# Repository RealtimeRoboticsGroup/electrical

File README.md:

# Realtime Robotic Group Electrical Repo

## License

This project is open-source hardware and is licensed under the **Solderpad Hardware License v2.1** (the "License"), which is a permissive license based on the **Apache License, Version 2.0**.

You may use this work under the terms of the Solderpad Hardware License v2.1, or, at your option, under the terms of the Apache License, Version 2.0.

- **Solderpad v2.1:** [Solderpad Hardware License v2.1 - Solderpad Hardware License](https://solderpad.org/licenses/SHL-2.1/)

- **Apache 2.0:** https://www.apache.org/licenses/LICENSE-2.0

**SPDX-License-Identifier:** `Apache-2.0 WITH SHL-2.1`

## License notes for included projects

### 1. For Schematics (Text Block)

Place this near your **Title Block** or in the **Notes** section of your first sheet.

> **LEGAL NOTICE** Copyright © 2026 [Your Name/Organization].
> Licensed under the Solderpad Hardware License v2.1 (the "License");
> you may not use this work except in compliance with the License.
> You may obtain a copy of the License at: [Solderpad Hardware License v2.1 - Solderpad Hardware License](https://solderpad.org/licenses/SHL-2.1/) SPDX-License-Identifier: Apache-2.0 WITH SHL-2.1

### 2. For PCB Silkscreen (Copper/Ink)

Space on a PCB is usually at a premium. You can use this condensed version on the back of the board (Bottom Silkscreen):

> **© 2026 [Your Name]** **Licensed under Solderpad v2.1** **[https://solderpad.org/SHL-2.1/](https://www.google.com/search?q=https://solderpad.org/SHL-2.1/)**

### 3. The OSHWA Logo (The "Gear")

If you want to signal that this is open-source hardware visually, it is common practice to add the **Open Source Hardware Logo** (a gear with a missing tooth) next to the license text. Most CAD libraries (like the SparkFun or Adafruit libraries) already have this logo as a "footprint" you can simply drop onto your board.

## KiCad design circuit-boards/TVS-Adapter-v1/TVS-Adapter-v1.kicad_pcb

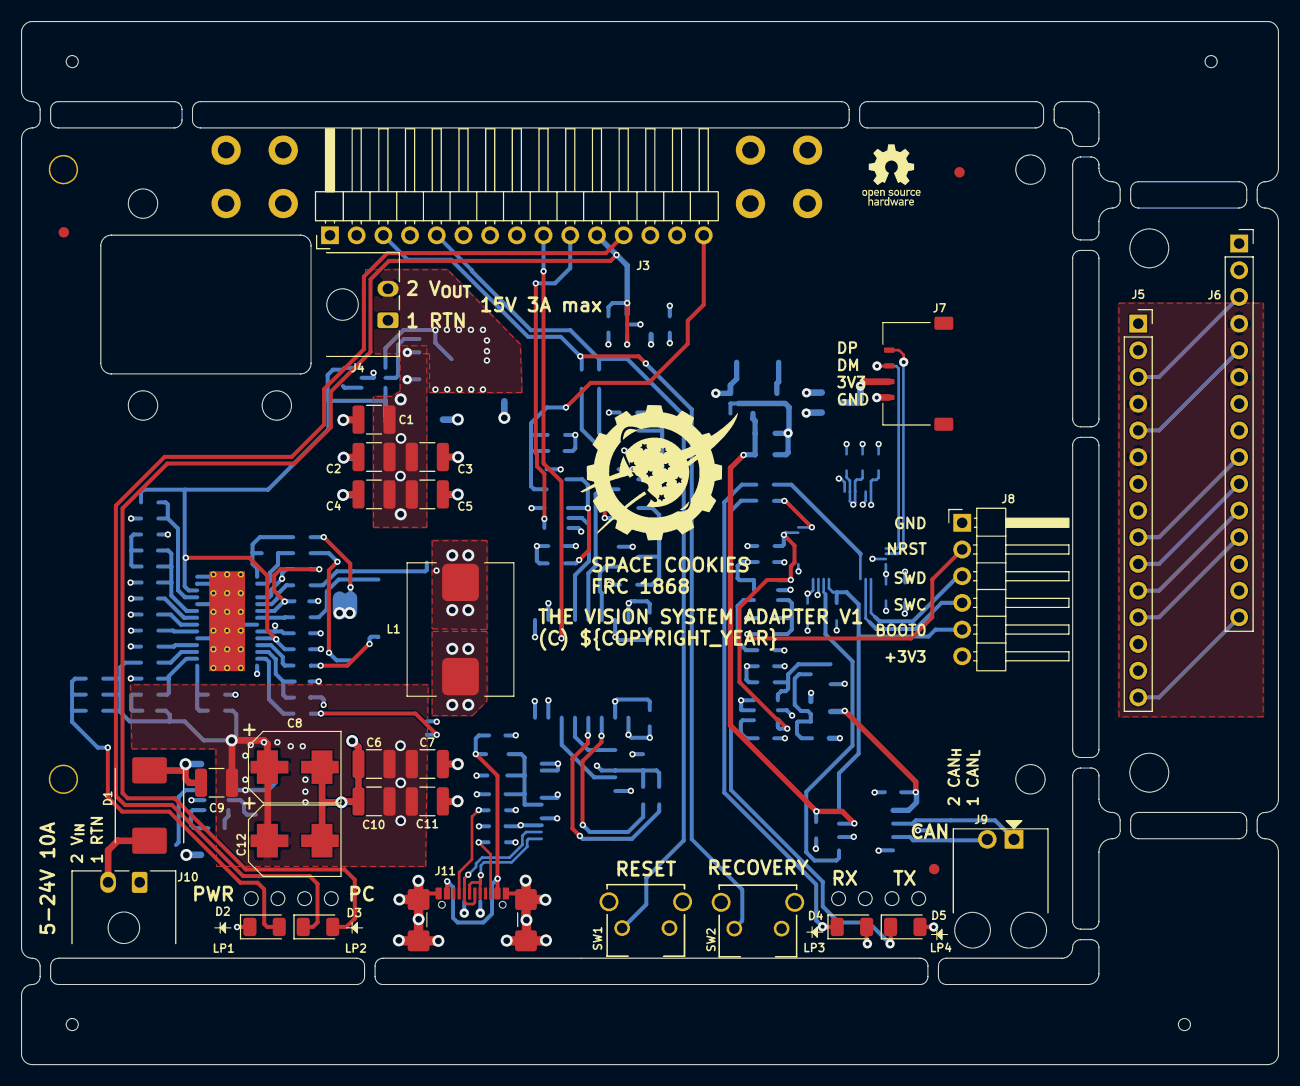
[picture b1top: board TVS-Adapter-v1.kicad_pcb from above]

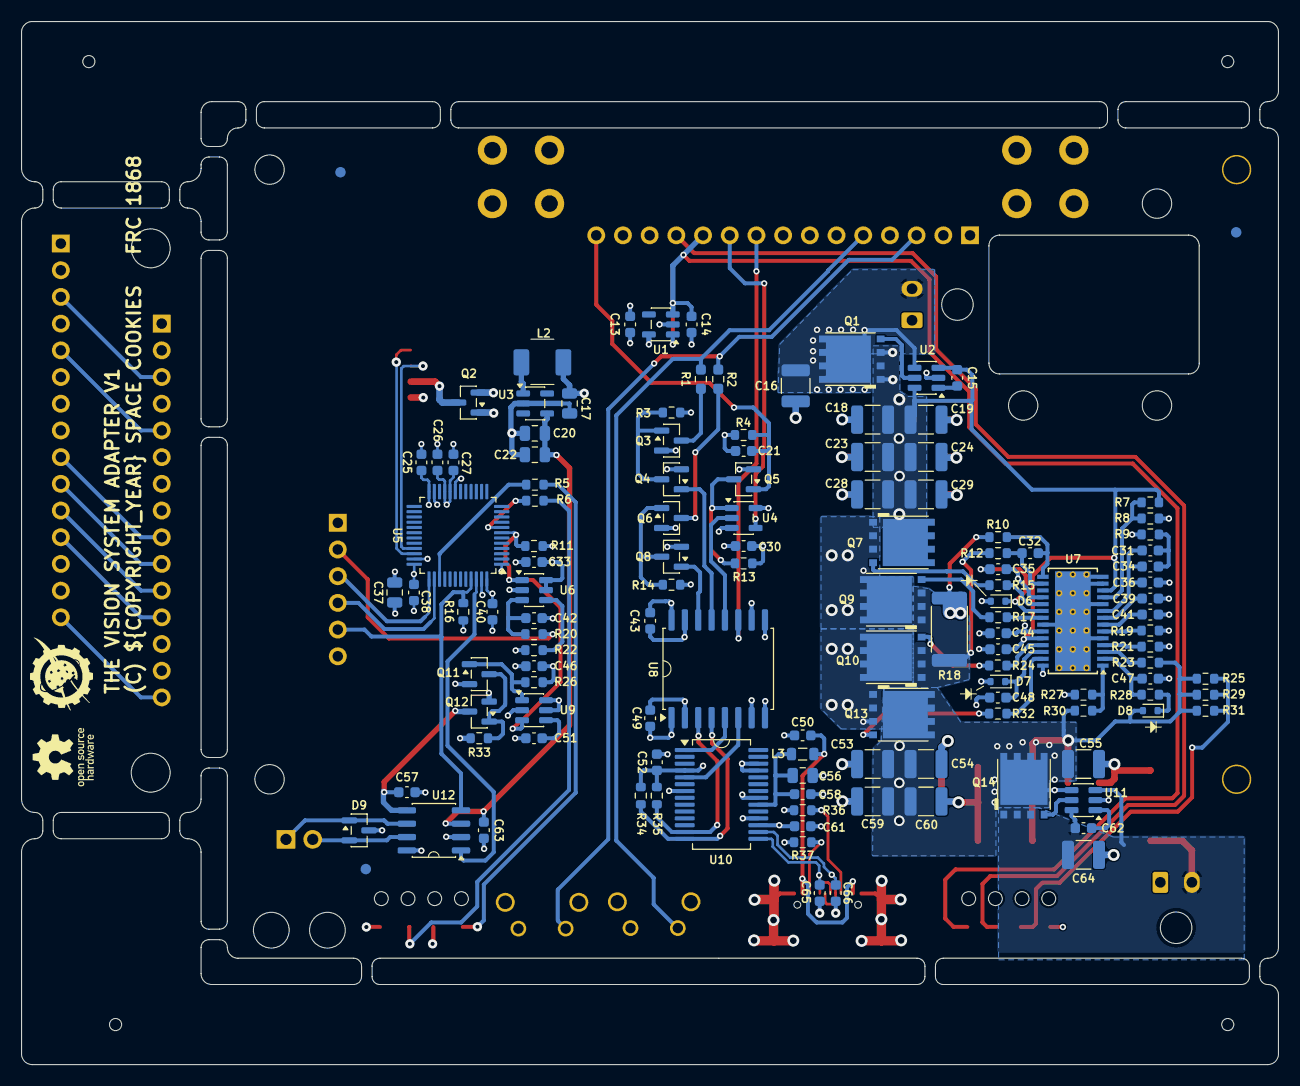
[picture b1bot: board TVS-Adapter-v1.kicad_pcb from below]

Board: 4 copper layers, 119.6 x 99.2 mm, 179 parts (127 on the bottom side), 99 nets.

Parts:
C1, C2, C3, C4, C5, C6, C7, C9, C10, C11, C16, C18, C19, C23, C24, C28, C29, C53, C54, C55, C59, C60, C64: 10uF-50V-10%-X7R-1210; C_1210_3225Metric
C8, C12: 47uF 50V; Panasonic-EEE-FT1H470AV
C13, C14, C44: 1uF-50V-10%-0603; C_0603_1608Metric
C15, C21, C25, C26, C27, C30, C33, C35, C38, C40, C43, C45, C46, C47, C48, C49, C51, C52, C57, C58, C61, C62, C63: 0.1uF-50V-10%-0603; C_0603_1608Metric
C17, C20, C22, C37, C56: 22uF-10%-16V-0805; C_0805_2012Metric
C31, C34: 5.6nF-10%-50V-0603; C_0603_1608Metric
C32, C65, C66: 47pF-50V-10%-0603; C_0603_1608Metric
C36: 270pF-10%-50V-0603; C_0603_1608Metric
C39, C42, C50: 15nF-10%-50V-0603; C_0603_1608Metric
C41: 150pF-50V-10%-0603; C_0603_1608Metric
D1: 24V; D_SMC_Littelfuse_DO-214AB
D2: PWR; LED_1206_3216Metric
D3: PC; LED_1206_3216Metric
D4: RX; LED_1206_3216Metric
D5: TX; LED_1206_3216Metric
D6, D7, D8: BAT54KFILM; D_SOD-523
D9: PESD1CAN; SOT-23
FID1, FID2, FID3, FID4, FID5, FID6: Fiducial; Fiducial_1mm_Mask3mm
H1, H2, H12, H13: 1.152mm ToolingHole; ToolingHole_1.152mm
H3, H4, H5, H7, H8, H10, H11: MountingHole; MountingHole_2.5mm
H6, H9: M3.7 MountingHole; MountingHole_3.7mm
J1, J2: Terminal; Keystone-7774
J3: NX CONTROL & UART; PinHeader_1x15_P2.54mm_Horizontal
J4: 15V; Molex_Micro-Fit_3.0_43650-0200_1x02_P3.00mm_Horizontal
J5, J6: NX CONTROL & UART; PinSocket_1x15_P2.54mm_Vertical
J7: USB1; Molex-PicoLatch-5040500491
J8: SWD; PinHeader_1x06_P2.54mm_Horizontal
J9: CAN1; Molex-70555-0001
J10: POWER; Molex_Micro-Fit_3.0_43650-0200_1x02_P3.00mm_Horizontal
J11: USB_C_Receptacle_USB2.0_14P; GCT-USB-C-USB4110-GF-A
L1: 2.2uH-19A-5.1mohm-20%; Koher-MDA1050
L2: 2.2uH-41mOhm-20%; KOHER-MDA4020-2R2M
L3: HZ0805E601R-10; L_0805_2012Metric
LOGO1: SPACE COOKIES LOGO; SPACE_COOKIES_LOGO_15mm
LOGO2: SPACE COOKIES LOGO; SPACE_COOKIES_LOGO_7mm
LP1, LP2, LP3, LP4: Light Pipe; Bivar-SLP3-150-100-F
Q1, Q10, Q13, Q14: CSD19534Q5A; TI-SON5x6
Q2, Q12: SI2301CDS-T1-GE3; SOT-23
Q3, Q4, Q5, Q6, Q8, Q11: BSS138; SOT-23
Q7, Q9: CSD17578Q5A; TI-SON5x6
R1, R2: 0R-1%-0603; R_0603_1608Metric_Pad0.98x0.95mm_HandSolder
R3, R4, R13, R14, R25, R29, R31, R34, R35, R36, R37: 5.1k-1%-0603; R_0603_1608Metric
R5, R6, R20: 1K-1%-0603; R_0603_1608Metric
R7: 357K-1%-0603; R_0603_1608Metric
R8: 20K-1%-0603; R_0603_1608Metric
R9: 5.9k-1%-0603; R_0603_1608Metric
R10, R12: 100R-1%-0603; R_0603_1608Metric
R11, R16, R19, R26: 13K-1%-0603; R_0603_1608Metric
R15, R17, R24, R32: 0R-1%-0603; R_0603_1608Metric
R18: 10mOhm-3W-1%-2512; R_2512_6332Metric
R21, R22, R27, R33: 93.1k-1%-0603; R_0603_1608Metric
R23: 2K-1%-0603; R_0603_1608Metric
R28: 10R0-1%-0603; R_0603_1608Metric
R30: 249K-1%-0603; R_0603_1608Metric
SW1: RESET; SW_TL1105VF100Q_EWI
SW2: RECOVERY; SW_TL1105VF100Q_EWI
U1: TLV70233DBVR; SOT-23-5
U2, U11: LM74700QDBVRQ1; SOT-23-6
U3: TPS613222ADBV; SOT-23-5
U4: SN74LVC1G125DBVR; SOT-23-5
U5: STM32G431CBTx; LQFP-48_7x7mm_P0.5mm
U6, U9: TPS3808G30DBVR; SOT-23-6
U7: LM5176PWPR; HTSSOP-28-1EP_4.4x9.7mm_P0.65mm_EP3.4x9.5mm_ThermalVias
U8: ISO6741DWR; SOIC-16W_7.5x10.3mm_P1.27mm
U10: FT232RNL; SSOP-28_5.3x10.2mm_P0.65mm
U12: TJA1051T/3/1J; SO-8_3.9x4.9mm_P1.27mm

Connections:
3V3_USB: C49.1, C52.1, C61.1, R34.2, R35.2, U8.1 (V_{CC1}), U8.7 (EN1), U10.4 (VCCIO), U10.17 (3V3OUT)
/3V3_BTN: C21.1, J3.15, Q5.1 (G), R4.2
/15V 3A Buck-Boost Power Supply/+V_OUT: C1.1, C2.1, C3.1, C4.1, C5.1, C15.1, C18.1, C19.1, C23.1, C24.1, C28.1, C29.1, C45.1, Q1.1 (S), Q1.2 (S), Q1.3 (S), Q7.5 (D), R7.1, U2.3 (EN), U2.6 (A), U7.12 (VOSNS), U7.24 (BIAS)
/15V 3A Buck-Boost Power Supply/HDRV1: Q13.4 (G), R32.2
/15V 3A Buck-Boost Power Supply/HDRV2: Q7.4 (G), R15.2
/15V 3A Buck-Boost Power Supply/LDRV1: Q10.4 (G), R24.2
/15V 3A Buck-Boost Power Supply/LDRV2: Q9.4 (G), R17.2
/15V 3A Buck-Boost Power Supply/RCS: Q9.1 (S), Q9.2 (S), Q9.3 (S), Q10.1 (S), Q10.2 (S), Q10.3 (S), R12.2, R18.1
/15V 3A Buck-Boost Power Supply/SW1: C48.2, L1.1, Q10.5 (D), Q13.1 (S), Q13.2 (S), Q13.3 (S), U7.28 (SW1)
/15V 3A Buck-Boost Power Supply/SW2: C35.2, L1.2, Q7.1 (S), Q7.2 (S), Q7.3 (S), Q9.5 (D), U7.18 (SW2)
/15V 3A Buck-Boost Power Supply/Vcc: C44.1, D6.2 (A), D7.2 (A), U7.23 (VCC)
/CANable2.0/3V3: C17.1, C25.1, C26.1, C27.1, C33.1, C37.1, C38.1, C40.1, C46.1, D4.2 (A), D5.2 (A), J8.6, L2.1, Q2.2 (S), Q12.2 (S), R11.1, R22.1, R26.1, R33.1, U5.1 (VBAT), U5.20 (VREF+), U5.21 (VDDA), U5.24 (VDD), U5.36 (VDD), U5.48 (VDD), U6.5 (SENSE), U6.6 (VDD), U9.5 (SENSE), U9.6 (VDD)
/CANable2.0/3V3_CAN: C57.1, Q12.3 (D), U12.5 (VIO)
/CANable2.0/3V3_USB: J7.2, Q2.3 (D)
/CANable2.0/5V_CAN: C20.1, C22.1, C63.1, U3.4 (VOUT), U12.3 (VCC)
/CANable2.0/BOOT0: J8.5, R16.1, U5.45 (FDCAN1_RX), U12.4 (RXD)
/CANable2.0/CAN_H: D9.2 (K1), J9.2, U12.7 (CANH)
/CANable2.0/CAN_L: D9.1 (K1), J9.1, U12.6 (CANL)
/CANable2.0/CAN_TX: U5.46 (FDCAN1_TX), U12.1 (TXD)
/CANable2.0/LED1: R5.2, U5.39 (PA15)
/CANable2.0/LED2: R6.2, U5.8 (PA0)
/CANable2.0/NRST: R11.2, U5.7 (PG10), U6.1 (~RESET), U9.3 (~MR)
/CANable2.0/SWCLK: J8.4, U5.38 (SYS_JTCK-SWCLK)
/CANable2.0/SWDIO: J8.3, U5.37 (SYS_JTMS-SWDIO)
/CANable2.0/USB_DM: J7.3, U5.33 (USB_DM)
/CANable2.0/USB_DP: J7.4, U5.34 (USB_DP)
/CANable2.0/~RESET: J8.2, R20.1
/NX-Button Interface/3V3_BTN: J5.15, J6.15
/NX-Button Interface/GND_BTN: J5.4, J5.6, J6.4, J6.6
/NX-Button Interface/NX_PC_LED+: J5.11, J6.11
/NX-Button Interface/NX_PC_LED-: J5.12, J6.12
/NX-Button Interface/UART2_RXD: J5.10, J6.10
/NX-Button Interface/UART2_TXD: J5.9, J6.9
/NX-Button Interface/~REC: J5.3, J6.3
/NX-Button Interface/~SYS_RESET: J5.5, J6.5
/NX_PC_LED-: D3.1 (K), J3.12
/UART2_RXD: J3.10, U4.4
/UART2_TXD: J3.9, U8.11 (IND)
/USB Serial/3V3: C13.1, C30.1, C43.1, R3.2, R13.2, R14.2, U1.5 (OUT), U4.5 (VCC), U8.10 (EN2), U8.16 (V_{CC2})
/VDD_5V_SYS: C14.1, D3.2 (A), J3.11, U1.1 (IN), U1.3 (EN)
/VIN_PS: C6.1, C7.1, C8.1, C9.1, C10.1, C11.1, C12.1, C53.1, C54.1, C55.1, C59.1, C60.1, D8.2 (A), Q13.5 (D), Q14.5 (D), R23.1, R25.2, R29.2, R30.1, R31.2, U11.4 (C)
/V_IN: C62.1, C64.1, D1.2 (A2), J10.2, Q14.1 (S), Q14.2 (S), Q14.3 (S), U11.3 (EN), U11.6 (A)
/V_OUT: C16.1, J4.2, Q1.5 (D), U2.4 (C)
/~REC: J3.3, R2.2, SW2.1
/~SYS_RESET: J3.5, R1.2, SW1.1
GND: C1.2, C2.2, C3.2, C4.2, C5.2, C6.2, C7.2, C8.2, C9.2, C10.2, C11.2, C12.2, C16.2, C18.2, C19.2, C23.2, C24.2, C28.2, C29.2, C36.2, C39.2, C41.2, C44.2, C45.2, C47.2, C53.2, C54.2, C55.2, C59.2, C60.2, C64.2, D1.1 (A1), D2.1 (K), J4.1, J10.1, R8.2, R9.2, R10.1, R18.2, R19.2, R21.2, R27.2, U2.2 (GND), U7.5 (DITH), U7.10 (AGND), U7.13 (ISNS(-)), U7.14 (ISNS(+)), U7.22 (PGND), U7.EP (PGND), U11.2 (GND)
GND1: C13.2, C14.2, C21.2, C30.2, C43.2, J3.4, J3.6, Q3.2 (S), Q4.2 (S), Q5.2 (S), Q6.2 (S), Q8.2 (S), R4.1, SW1.2, SW2.2, U1.2 (GND), U4.3 (GND), U8.9 (GND2), U8.15 (GND2)
GND_CAN: C17.2, C20.2, C22.2, C25.2, C26.2, C27.2, C33.2, C37.2, C38.2, C40.2, C42.2, C46.2, C51.2, C57.2, C63.2, D9.3 (KK), J7.1, J8.1, Q2.1 (G), Q11.2 (S), R16.2, U3.2 (GND), U5.19 (VSSA), U5.23 (VSS), U5.35 (VSS), U5.47 (VSS), U6.2 (GND), U9.2 (GND), U12.2 (GND), U12.8 (S)
GND_USB: C49.2, C50.2, C52.2, C56.2, C58.2, C61.2, C65.2, C66.2, J11.A1B12 (GND), J11.B1A12 (GND), J11.S1 (SHIELD), R36.2, R37.2, U8.2 (GND1), U8.8 (GND1), U10.7 (GND), U10.18 (GND), U10.21 (GND), U10.25 (AGND), U10.26 (TEST)
unnamed: C31.2, C34.2, R9.1
unnamed: C50.1, J11.A4B9 (VBUS), J11.B4A9 (VBUS), L3.1
unnamed: D2.2 (A), R25.1, R29.1, R31.1
unnamed: D4.1 (K), R5.1
unnamed: D5.1 (K), R6.1
unnamed: C35.1, D6.1 (K), U7.20 (BOOT2)
unnamed: C48.1, D7.1 (K), U7.26 (BOOT1)
unnamed: D8.1 (K), R28.1
unnamed: J11.A5 (CC1), R36.1
unnamed: J11.B5 (CC2), R37.1
unnamed: Q1.4 (G), U2.5 (G)
unnamed: Q3.3 (D), R1.1
unnamed: Q3.1 (G), Q4.3 (D), R3.1
unnamed: Q4.1 (G), U8.13 (OUTB)
unnamed: Q5.3 (D), R13.1, U4.1
unnamed: Q6.3 (D), R2.1
unnamed: Q6.1 (G), Q8.3 (D), R14.1
unnamed: Q8.1 (G), U8.14 (OUTA)
unnamed: Q11.3 (D), Q12.1 (G), R33.2
unnamed: Q11.1 (G), R26.2, U9.1 (~RESET)
unnamed: Q14.4 (G), U11.5 (G)
unnamed: C15.2, U2.1 (VCAP)
unnamed: L2.2, U3.1 (SW)
unnamed: R22.2, U6.4 (CT)
unnamed: C42.1, R20.2, U6.3 (~MR)
unnamed: C31.1, C34.1, C36.1, U7.9 (COMP)
unnamed: C32.1, R12.1, U7.16 (CS)
unnamed: C32.2, R10.2, U7.15 (CSG)
unnamed: R27.1, R30.2, U7.1 (EN/UVLO)
unnamed: R7.2, R8.1, U7.11 (FB)
unnamed: R32.1, U7.27 (HDRV1)
unnamed: R15.1, U7.19 (HDRV2)
unnamed: R24.1, U7.25 (LDRV1)
unnamed: R17.1, U7.21 (LDRV2)
unnamed: R21.1, U7.4 (MODE)
unnamed: R19.1, U7.6 (RT)
unnamed: C41.1, U7.7 (SLOPE)
unnamed: C39.1, U7.8 (SS)
unnamed: C47.1, R28.2, U7.2 (VIN)
unnamed: R23.2, U7.3 (VISNS)
unnamed: U4.2, U8.12 (OUTC)
unnamed: C51.1, U9.4 (CT)
unnamed: R35.1, U8.3 (INA), U10.13 (CBUS2)
unnamed: R34.1, U8.4 (INB), U10.14 (CBUS3)
unnamed: U8.6 (OUTD), U10.5 (RXD)
unnamed: U8.5 (INC), U10.1 (TXD)
unnamed: C65.1, J11.A6 (D+), J11.B6 (D+), U10.15 (USBD+)
unnamed: C66.1, J11.A7 (D-), J11.B7 (D-), U10.16 (USBD-)
unnamed: C56.1, C58.1, L3.2, U10.20 (VCC)
unnamed: C62.2, U11.1 (VCAP)

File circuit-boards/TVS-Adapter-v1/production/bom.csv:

Designator,Footprint,Quantity,Value,LCSC Part #
"C1, C10, C11, C16, C18, C19, C2, C23, C24, C28, C29, C3, C4, C5, C53, C54, C55, C59, C6, C60, C64, C7, C9",1210,23,10uF-50V-10%-X7R-1210,C77102
"C12, C8",Panasonic-EEE-FT1H470AV,2,47uF 50V,XXXXXX
"C13, C14, C44",0603,3,1uF-50V-10%-0603,C105174
"C15, C21, C25, C26, C27, C30, C33, C35, C38, C40, C43, C45, C46, C47, C48, C49, C51, C52, C57, C58, C61, C62, C63, C65",0603,24,0.1uF-50V-10%-0603,C14663
"C17, C20, C22, C37, C56",0805,5,22uF-10%-16V-0805,C296720
"C31, C34",0603,2,5.6nF-10%-50V-0603,C107095
"C32, C66, C67",0603,3,47pF-50V-10%-0603,C2168903
C36,0603,1,270pF-10%-50V-0603,C107084
"C39, C42, C50",0603,3,15nF-10%-50V-0603,C107076
C41,0603,1,150pF-50V-10%-0603,C107075
D1,D_SMC_Littelfuse_DO-214AB,1,24V,C284061
D2,1206,1,PWR,C5123493
D3,1206,1,PC,C5123493
D4,1206,1,RX,C965824
D5,1206,1,TX,C965824
"D6, D7, D8",D_SOD-523,3,BAT54KFILM,C283259
D9,SOT-23,1,PESD1CAN,C15771
"J1, J2",Keystone-7774,2,Terminal,XXXXXX
J10,Molex_Micro-Fit_3.0_43650-0200_1x02_P3.00mm_Horizontal,1,POWER,XXXXXX
J11,GCT-USB-C-USB4110-GF-A,1,USB_C_Receptacle_USB2.0_14P,C5143397
J3,PinHeader_1x15_P2.54mm_Horizontal,1,NX CONTROL & UART,XXXXXX
"J4, J6",PinSocket_1x15_P2.54mm_Vertical,2,NX CONTROL & UART,XXXXXX
J5,Molex_Micro-Fit_3.0_43650-0200_1x02_P3.00mm_Horizontal,1,15V,XXXXXX
J7,Molex-PicoLatch-5040500491,1,USB1,C177235
J8,PinHeader_1x06_P2.54mm_Horizontal,1,SWD,XXXXXX
J9,Molex-70555-0001,1,CAN1,XXXXXX
L1,Koher-MDA1050,1,2.2uH-19A-5.1mohm-20%,C2847559
L2,KOHER-MDA4020-2R2M,1,2.2uH-41mOhm-20%,C2847469
L3,0805,1,HZ0805E601R-10,C2441364
"LP1, LP2, LP3, LP4",Bivar-SLP3-150-100-F,4,Light Pipe,XXXXXX
"Q1, Q10, Q13, Q14",TI-SON5x6,4,CSD19534Q5A,C114200
"Q11, Q3, Q4, Q5, Q6, Q8",SOT-23,6,BSS138,C52895
"Q12, Q2",SOT-23,2,SI2301CDS-T1-GE3,C10487
"Q7, Q9",TI-SON5x6,2,CSD17578Q5A,C2871447
"R10, R12",0603,2,100R-1%-0603,C105588
"R11, R16, R19, R26",0603,4,13K-1%-0603,C137796
"R13, R14, R25, R29, R3, R31, R34, R35, R36, R37, R4",0603,11,5.1k-1%-0603,C105580
"R15, R17, R24, R32",0603,4,0R-1%-0603,C100044
R18,2512,1,10mOhm-3W-1%-2512,C723413
"R20, R5, R6",0603,3,1K-1%-0603,C22548
"R21, R22, R27, R33",0603,4,93.1k-1%-0603,C228101
R23,0603,1,2K-1%-0603,C105576
R28,0603,1,10R0-1%-0603,C109318
R30,0603,1,249K-1%-0603,C706146
R7,0603,1,357K-1%-0603,C227834
R8,0603,1,20K-1%-0603,C105575
R9,0603,1,5.9k-1%-0603,C23071
SW1,SW_TL1105VF100Q_EWI,1,RESET,XXXXXX
SW2,SW_TL1105VF100Q_EWI,1,RECOVERY,XXXXXX
U1,SOT-23-5,1,TLV70233DBVR,C26833
U10,SSOP-28_5.3x10.2mm_P0.65mm,1,FT232RNL,C5246810
"U11, U2",SOT-23-6,2,LM74700QDBVRQ1,C2941042
U12,SO-8_3.9x4.9mm_P1.27mm,1,TJA1051T/3/1J,C38695
U13,SOT-23-6,1,USBLC6-2SC6,C7519
U3,SOT-23-5,1,TPS613222ADBV,C2071163
U4,SOT-23-5,1,SN74LVC1G125DBVR,C23654
U5,LQFP-48_7x7mm_P0.5mm,1,STM32G431CBTx,C529355
"U6, U9",SOT-23-6,2,TPS3808G30DBVR,C189211
U7,HTSSOP-28-1EP_4.4x9.7mm_P0.65mm_EP3.4x9.5mm_ThermalVias,1,LM5176PWPR,C442493
U8,SOIC-16W_7.5x10.3mm_P1.27mm,1,ISO6741DWR,C5216432

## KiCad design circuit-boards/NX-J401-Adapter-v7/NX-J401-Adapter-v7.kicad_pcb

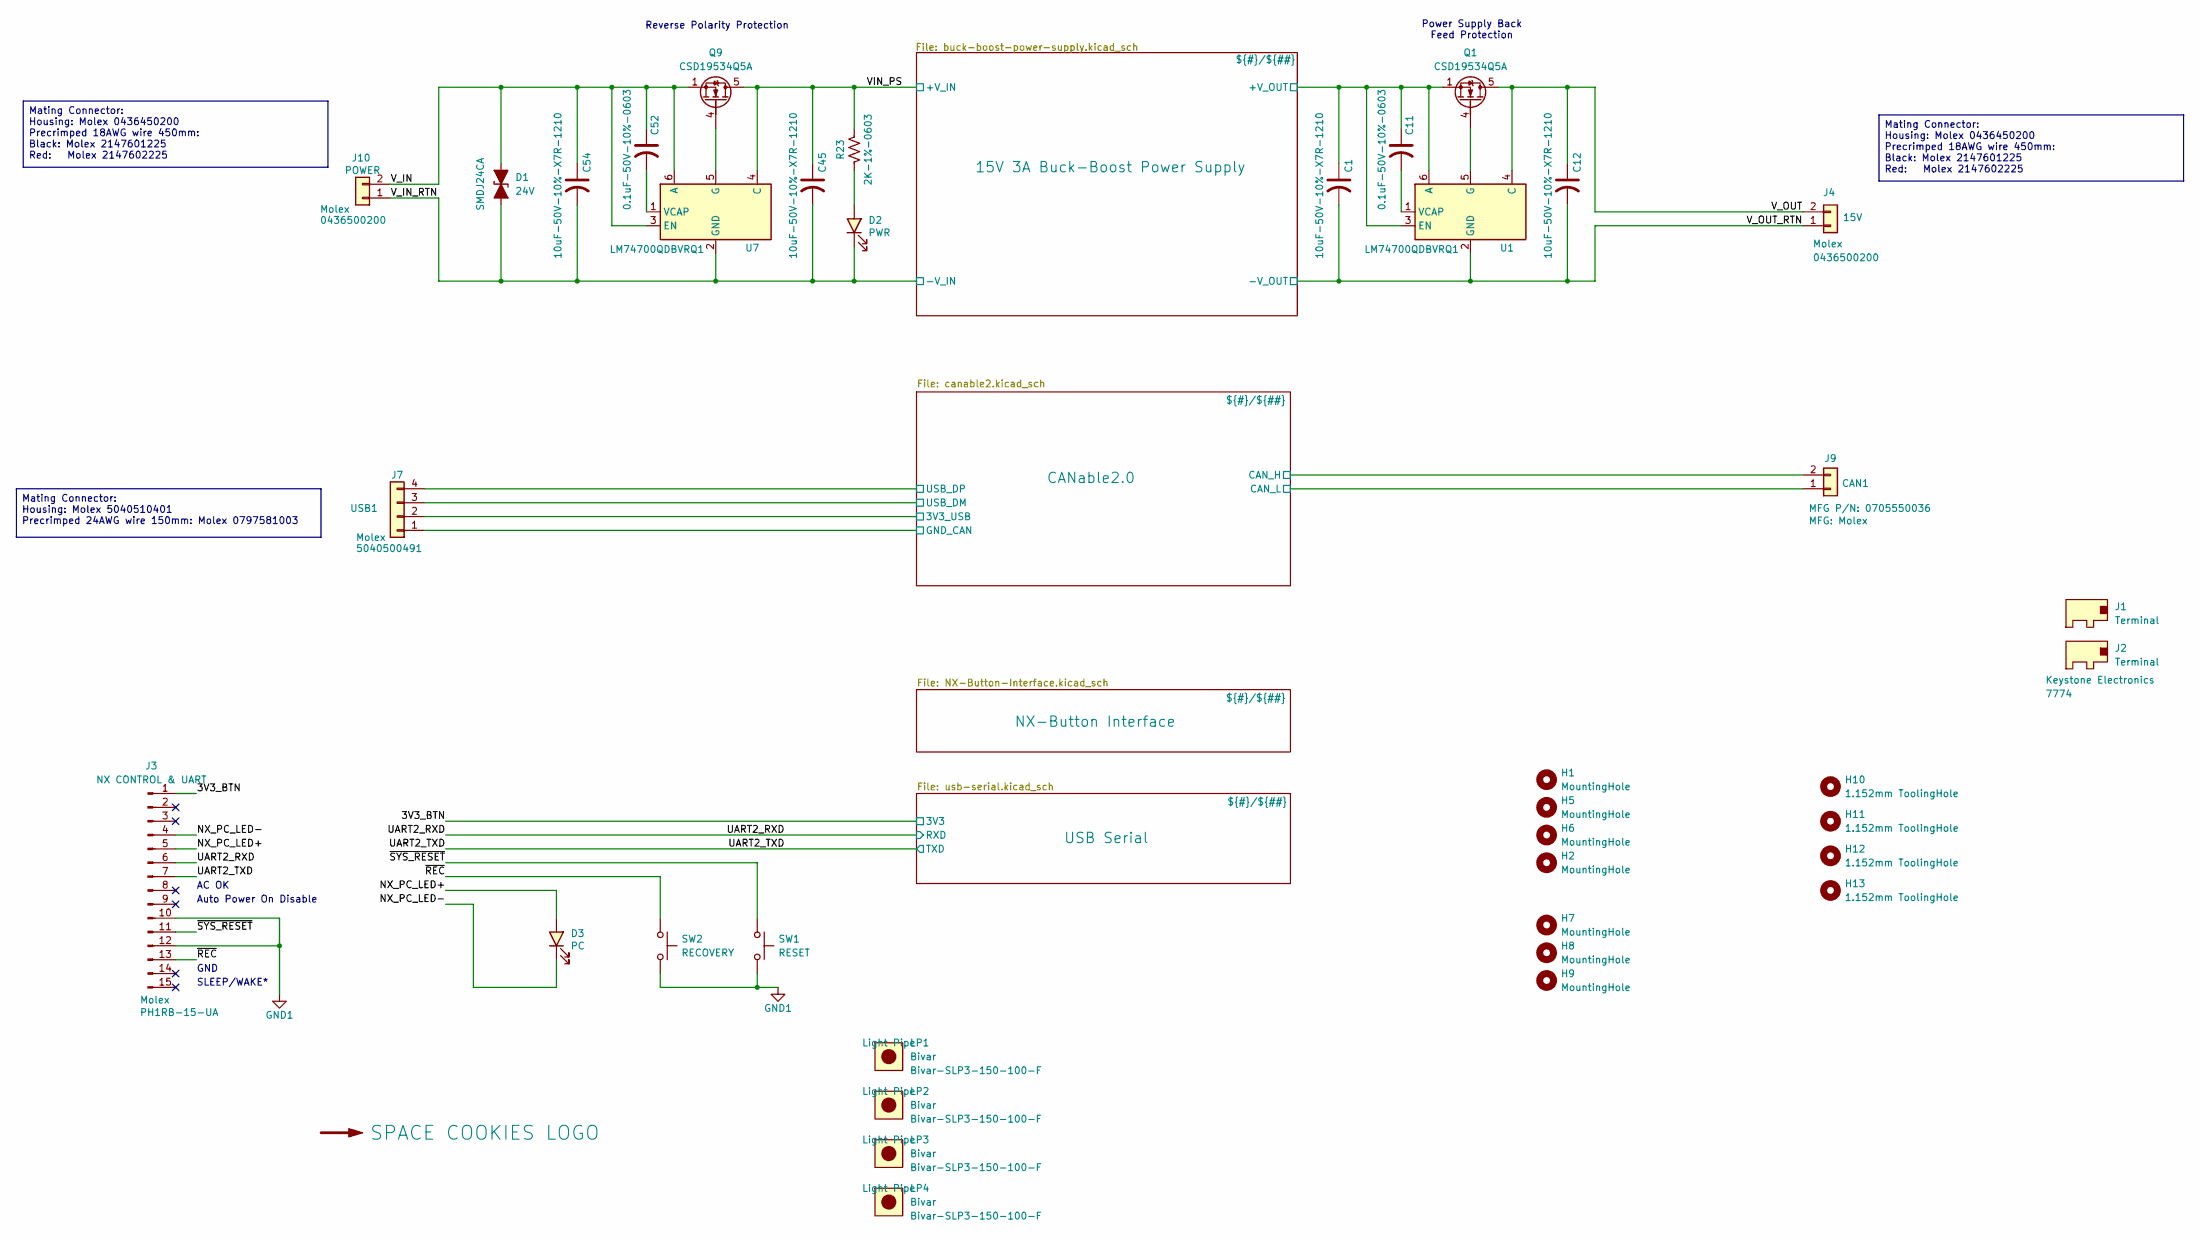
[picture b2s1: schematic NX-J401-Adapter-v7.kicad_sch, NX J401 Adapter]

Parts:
C1, C12, C45, C54: 10uF-50V-10%-X7R-1210; C_1210_3225Metric; MFG P/N GRM32ER71H106KA12L; JLCPCB P/N C77102
C11, C52: 0.1uF-50V-10%-0603; C_0603_1608Metric; MFG P/N CC0603KRX7R9BB104; JLCPCB P/N C14663
D1: 24V; D_SMC_Littelfuse_DO-214AB; MFG P/N SMDJ24CA; JLCPCB P/N C284061
D2: PWR; LED_1206_3216Metric; MFG P/N BL-HGK33-TRB; JLCPCB P/N C5123493
D3: PC; LED_1206_3216Metric; MFG P/N BL-HGK33-TRB; JLCPCB P/N C5123493
H1, H2, H5, H6, H7, H8, H9: MountingHole; MountingHole_2.5mm
H10, H11, H12, H13: 1.152mm ToolingHole; ToolingHole_1.152mm
J1, J2: Terminal; Keystone-7774; MFG P/N 7774; JLCPCB P/N XXXXXX
J3: NX CONTROL & UART; PinHeader_1x15_P2.54mm_Horizontal; MFG P/N PH1RB-15-UA; JLCPCB P/N XXXXXX
J4: 15V; Molex_Micro-Fit_3.0_43650-0200_1x02_P3.00mm_Horizontal; MFG P/N 0436500200; JLCPCB P/N XXXXXX
J7: USB1; Molex-PicoLatch-5040500491; MFG P/N 5040500491; JLCPCB P/N C177235
J9: CAN1; Molex-70555-0001; MFG P/N 0705550036; JLCPCB P/N XXXXXX
J10: POWER; Molex_Micro-Fit_3.0_43650-0200_1x02_P3.00mm_Horizontal; MFG P/N 0436500200; JLCPCB P/N XXXXXX
LOGO1: SPACE COOKIES LOGO; SPACE_COOKIES_LOGO_15mm
LP1, LP2, LP3, LP4: Light Pipe; Bivar-SLP3-150-100-F; MFG P/N Bivar-SLP3-150-100-F; JLCPCB P/N XXXXXX
Q1, Q9: CSD19534Q5A; TI-SON5x6; MFG P/N CSD19534Q5A; JLCPCB P/N C114200
R23: 2K-1%-0603; R_0603_1608Metric; MFG P/N RC0603FR-072KL; JLCPCB P/N C105576
SW1: RESET; SW_TL1105VF100Q_EWI; MFG P/N TL1105VF100Q; JLCPCB P/N XXXXXX
SW2: RECOVERY; SW_TL1105VF100Q_EWI; MFG P/N TL1105VF100Q; JLCPCB P/N XXXXXX
U1, U7: LM74700QDBVRQ1; SOT-23-6; MFG P/N LM74700QDBVRQ1; JLCPCB P/N C2941042

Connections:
/3V3_BTN: J3.1; also elsewhere on the board
/15V 3A Buck-Boost Power Supply/+V_OUT: C1.1, C11.1, Q1.1 (S), Q1.2 (S), Q1.3 (S), U1.3 (EN), U1.6 (A); also elsewhere on the board
/CANable2.0/3V3_USB: J7.2; also elsewhere on the board
/CANable2.0/CAN_H: J9.2; also elsewhere on the board
/CANable2.0/CAN_L: J9.1; also elsewhere on the board
/CANable2.0/GND_CAN: J7.1; also elsewhere on the board
/CANable2.0/USB_DM: J7.3; also elsewhere on the board
/CANable2.0/USB_DP: J7.4; also elsewhere on the board
/NX_PC_LED+: D3.2 (A), J3.5
/NX_PC_LED-: D3.1 (K), J3.4
/UART2_RXD: J3.6; also elsewhere on the board
/UART2_TXD: J3.7; also elsewhere on the board
/VIN_PS: C45.1, Q9.5 (D), R23.1, U7.4 (C); also elsewhere on the board
/V_IN: C52.1, C54.1, D1.2 (A2), J10.2, Q9.1 (S), Q9.2 (S), Q9.3 (S), U7.3 (EN), U7.6 (A)
/V_OUT: C12.1, J4.2, Q1.5 (D), U1.4 (C)
/~REC: J3.13, SW2.1
/~SYS_RESET: J3.11, SW1.1
GND: C1.2, C12.2, C45.2, C54.2, D1.1 (A1), D2.1 (K), J4.1, J10.1, U1.2 (GND), U7.2 (GND); also elsewhere on the board
GND1: J3.10, J3.12, SW1.2, SW2.2; also elsewhere on the board
unnamed: D2.2 (A), R23.2
unnamed: Q1.4 (G), U1.5 (G)
unnamed: Q9.4 (G), U7.5 (G)
unnamed: C11.2, U1.1 (VCAP)
unnamed: C52.2, U7.1 (VCAP)

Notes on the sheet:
GND
Power Supply Back Feed Protection
SLEEP/WAKE*
Reverse Polarity Protection
Auto Power On Disable
AC OK
Mating Connector: Housing: Molex 0436450200 Precrimped 18AWG wire 450mm: Black: Molex 2147601225 Red: Molex 2147602225
Mating Connector: Housing: Molex 5040510401 Precrimped 24AWG wire 150mm: Molex 0797581003

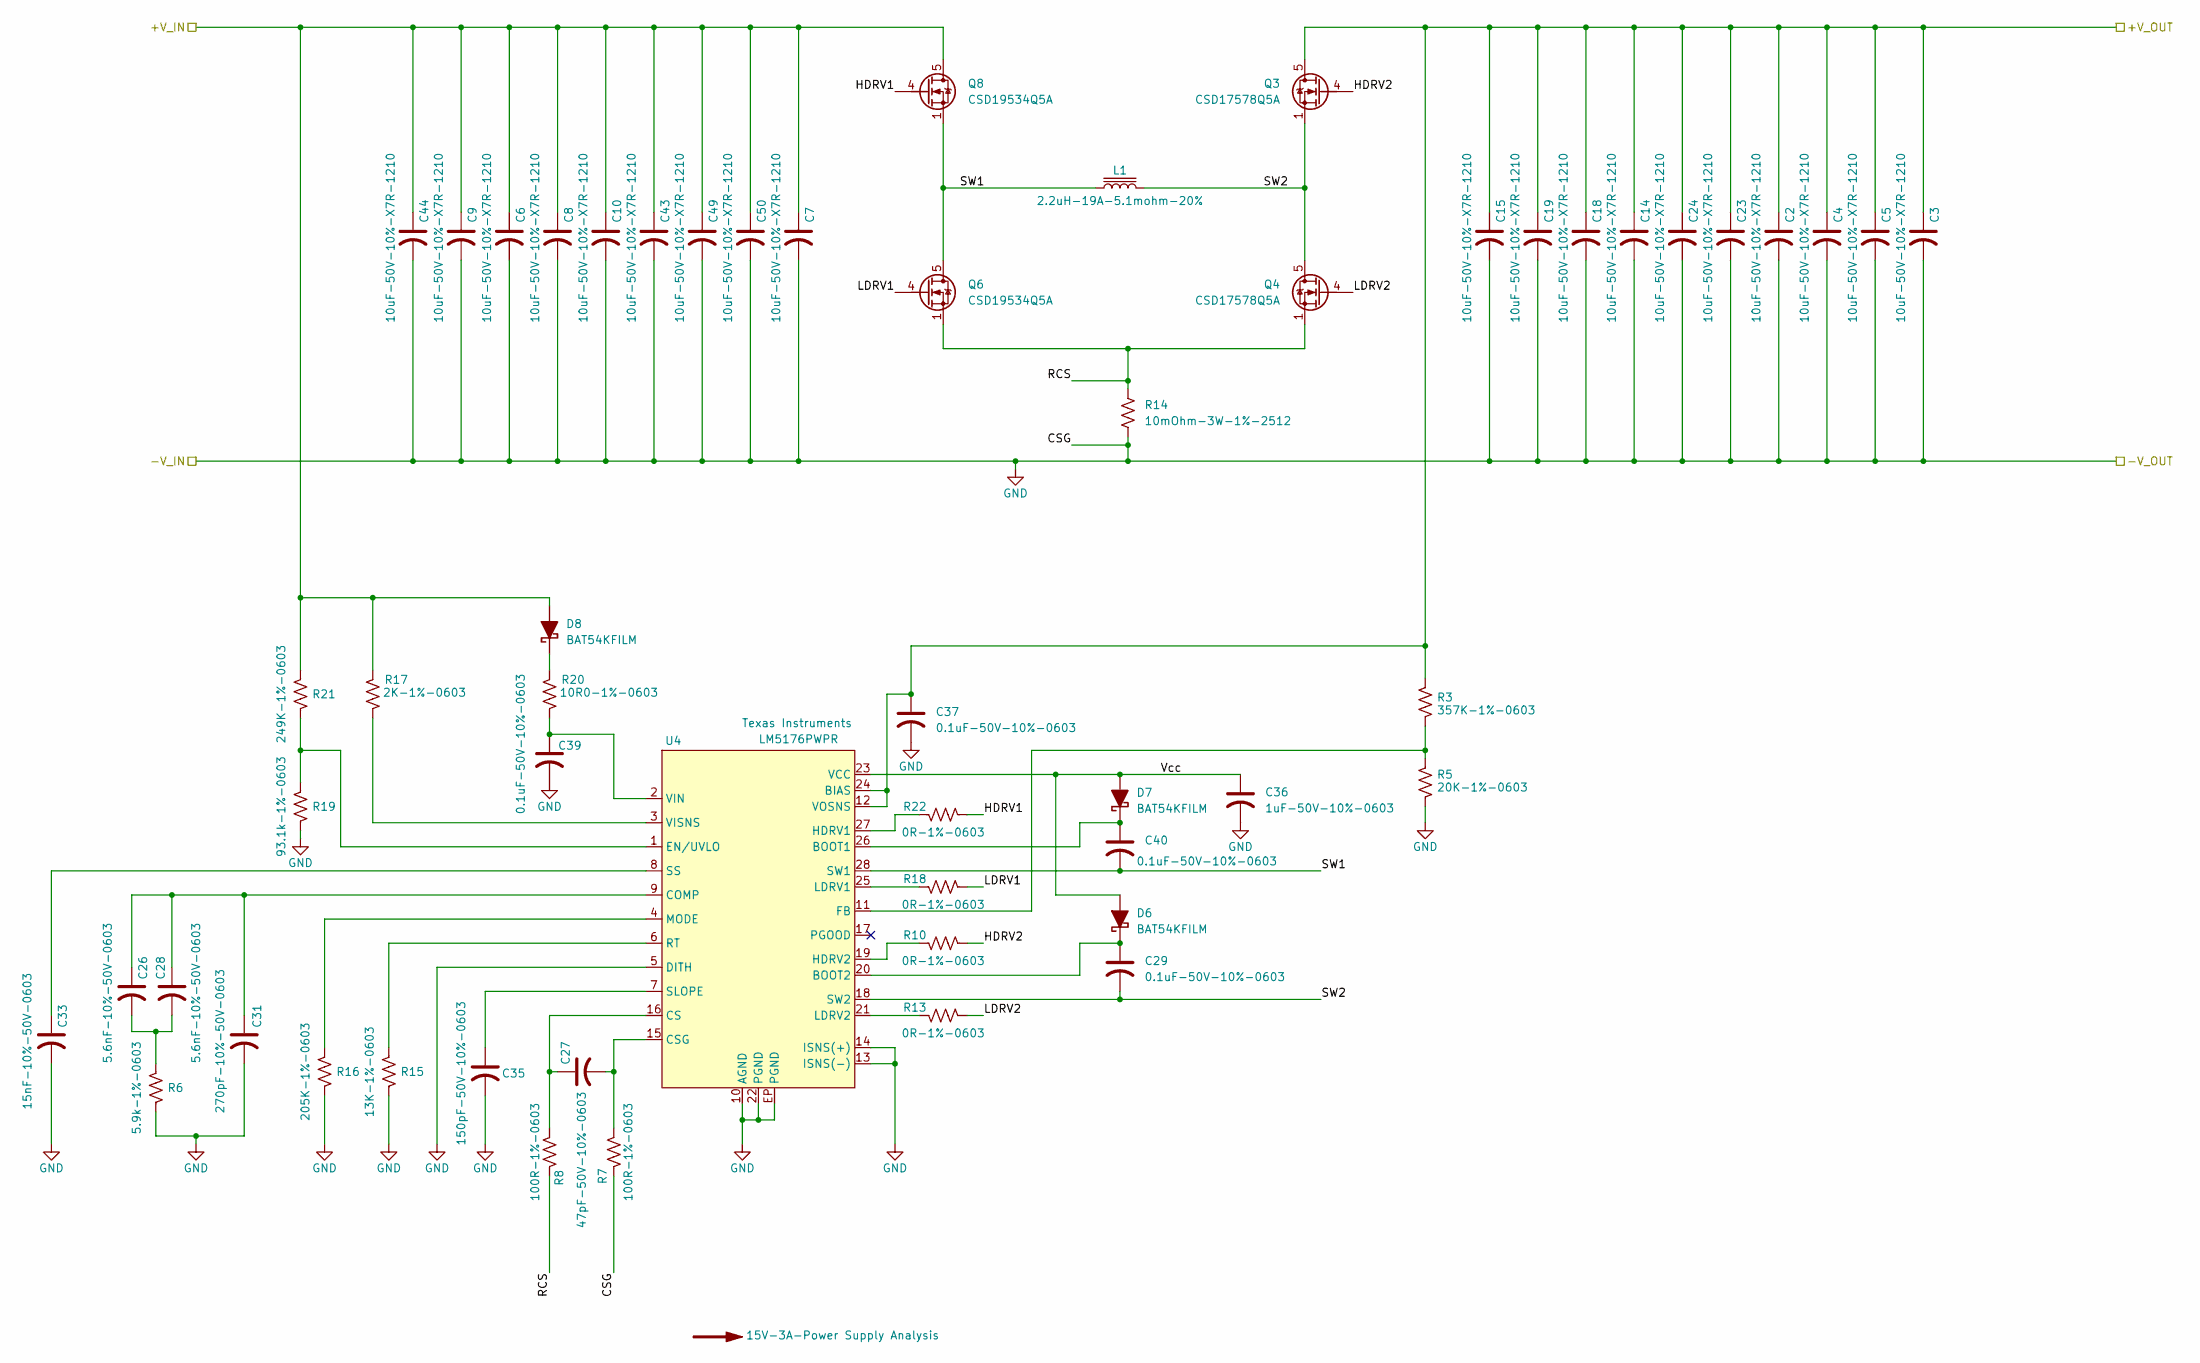
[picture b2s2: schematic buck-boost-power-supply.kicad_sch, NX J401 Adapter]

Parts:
C2, C3, C4, C5, C6, C7, C8, C9, C10, C14, C15, C18, C19, C23, C24, C43, C44, C49, C50: 10uF-50V-10%-X7R-1210; C_1210_3225Metric; MFG P/N GRM32ER71H106KA12L; JLCPCB P/N C77102
C26, C28: 5.6nF-10%-50V-0603; C_0603_1608Metric; MFG P/N CC0603KRX7R9BB562; JLCPCB P/N C107095
C27: 47pF-50V-10%-0603; C_0603_1608Metric; MFG P/N C0603C470K5GACAUTO; JLCPCB P/N C2168903
C29, C37, C39, C40: 0.1uF-50V-10%-0603; C_0603_1608Metric; MFG P/N CC0603KRX7R9BB104; JLCPCB P/N C14663
C31: 270pF-10%-50V-0603; C_0603_1608Metric; MFG P/N CC0603KRX7R9BB271; JLCPCB P/N C107084
C33: 15nF-10%-50V-0603; C_0603_1608Metric; MFG P/N CC0603KRX7R9BB153; JLCPCB P/N C107076
C35: 150pF-50V-10%-0603; C_0603_1608Metric; MFG P/N CC0603KRX7R9BB151; JLCPCB P/N C107075
C36: 1uF-50V-10%-0603; C_0603_1608Metric; MFG P/N UMK107AB7105KA-T; JLCPCB P/N C105174
D6, D7, D8: BAT54KFILM; D_SOD-523; MFG P/N STMicroelectronics; JLCPCB P/N C283259
L1: 2.2uH-19A-5.1mohm-20%; Koher-MDA1050; MFG P/N MDA1050-2R2M; JLCPCB P/N C2847559
Q3, Q4: CSD17578Q5A; TI-SON5x6; MFG P/N CSD17578Q5A; JLCPCB P/N C2871447
Q6, Q8: CSD19534Q5A; TI-SON5x6; MFG P/N CSD19534Q5A; JLCPCB P/N C114200
R3: 357K-1%-0603; R_0603_1608Metric; MFG P/N AC0603FR-07357KL; JLCPCB P/N C227834
R5: 20K-1%-0603; R_0603_1608Metric; MFG P/N RC0603FR-0720KL; JLCPCB P/N C105575
R6: 5.9k-1%-0603; R_0603_1608Metric; MFG P/N 0603WAF5901T5E; JLCPCB P/N C23071
R7, R8: 100R-1%-0603; R_0603_1608Metric; MFG P/N RC0603FR-07100RL; JLCPCB P/N C105588
R10, R13, R18, R22: 0R-1%-0603; R_0603_1608Metric; MFG P/N RC0603FR-070RL; JLCPCB P/N C100044
R14: 10mOhm-3W-1%-2512; R_2512_6332Metric; MFG P/N PA2512FKF7T0R01E; JLCPCB P/N C723413
R15: 13K-1%-0603; R_0603_1608Metric; MFG P/N RC0603FR-0713KL; JLCPCB P/N C137796
R16: 205K-1%-0603; R_0603_1608Metric; MFG P/N 0603WAF2053T5E; JLCPCB P/N C22949
R17: 2K-1%-0603; R_0603_1608Metric; MFG P/N RC0603FR-072KL; JLCPCB P/N C105576
R19: 93.1k-1%-0603; R_0603_1608Metric; MFG P/N AC0603FR-0793K1L; JLCPCB P/N C228101
R20: 10R0-1%-0603; R_0603_1608Metric; MFG P/N RC0603FR-0710RL; JLCPCB P/N C109318
R21: 249K-1%-0603; R_0603_1608Metric; MFG P/N RT0603FRE07249KL; JLCPCB P/N C706146
U4: LM5176PWPR; HTSSOP-28-1EP_4.4x9.7mm_P0.65mm_EP3.4x9.5mm_ThermalVias; MFG P/N LM5176PWPR; JLCPCB P/N C442493

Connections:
/15V 3A Buck-Boost Power Supply/+V_OUT: C2.1, C3.1, C4.1, C5.1, C14.1, C15.1, C18.1, C19.1, C23.1, C24.1, C37.1, Q3.5 (D), R3.1, U4.12 (VOSNS), U4.24 (BIAS); also elsewhere on the board
/15V 3A Buck-Boost Power Supply/HDRV1: Q8.4 (G), R22.2
/15V 3A Buck-Boost Power Supply/HDRV2: Q3.4 (G), R10.2
/15V 3A Buck-Boost Power Supply/LDRV1: Q6.4 (G), R18.2
/15V 3A Buck-Boost Power Supply/LDRV2: Q4.4 (G), R13.2
/15V 3A Buck-Boost Power Supply/RCS: Q4.1 (S), Q4.2 (S), Q4.3 (S), Q6.1 (S), Q6.2 (S), Q6.3 (S), R8.2, R14.1
/15V 3A Buck-Boost Power Supply/SW1: C40.2, L1.1, Q6.5 (D), Q8.1 (S), Q8.2 (S), Q8.3 (S), U4.28 (SW1)
/15V 3A Buck-Boost Power Supply/SW2: C29.2, L1.2, Q3.1 (S), Q3.2 (S), Q3.3 (S), Q4.5 (D), U4.18 (SW2)
/15V 3A Buck-Boost Power Supply/Vcc: C36.1, D6.2 (A), D7.2 (A), U4.23 (VCC)
/VIN_PS: C6.1, C7.1, C8.1, C9.1, C10.1, C43.1, C44.1, C49.1, C50.1, D8.2 (A), Q8.5 (D), R17.1, R21.1; also elsewhere on the board
GND: C2.2, C3.2, C4.2, C5.2, C6.2, C7.2, C8.2, C9.2, C10.2, C14.2, C15.2, C18.2, C19.2, C23.2, C24.2, C31.2, C33.2, C35.2, C36.2, C37.2, C39.2, C43.2, C44.2, C49.2, C50.2, R5.2, R6.2, R7.1, R14.2, R15.2, R16.2, R19.2, U4.5 (DITH), U4.10 (AGND), U4.13 (ISNS(-)), U4.14 (ISNS(+)), U4.22 (PGND), U4.EP (PGND); also elsewhere on the board
unnamed: C26.2, C28.2, R6.1
unnamed: C29.1, D6.1 (K), U4.20 (BOOT2)
unnamed: C40.1, D7.1 (K), U4.26 (BOOT1)
unnamed: D8.1 (K), R20.1
unnamed: C26.1, C28.1, C31.1, U4.9 (COMP)
unnamed: C27.1, R8.1, U4.16 (CS)
unnamed: C27.2, R7.2, U4.15 (CSG)
unnamed: R19.1, R21.2, U4.1 (EN/UVLO)
unnamed: R3.2, R5.1, U4.11 (FB)
unnamed: R22.1, U4.27 (HDRV1)
unnamed: R10.1, U4.19 (HDRV2)
unnamed: R18.1, U4.25 (LDRV1)
unnamed: R13.1, U4.21 (LDRV2)
unnamed: R16.1, U4.4 (MODE)
unnamed: R15.1, U4.6 (RT)
unnamed: C35.1, U4.7 (SLOPE)
unnamed: C33.1, U4.8 (SS)
unnamed: C39.1, R20.2, U4.2 (VIN)
unnamed: R17.2, U4.3 (VISNS)

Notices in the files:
circuit-boards/mag-encoder/mag-encoder.kicad_pcb:
(C)2025 1868
parts and their libraries:
Copyright 2021 Accelerated Designs. All rights reserved.
